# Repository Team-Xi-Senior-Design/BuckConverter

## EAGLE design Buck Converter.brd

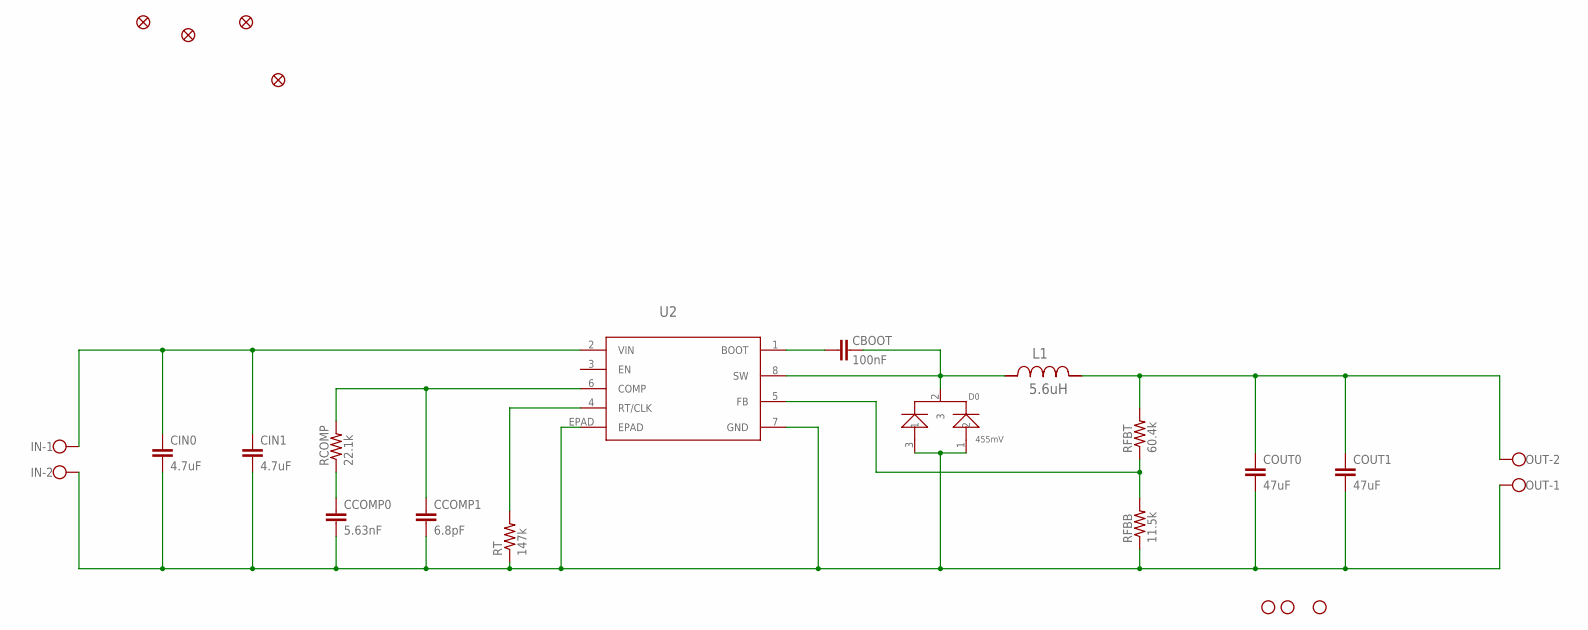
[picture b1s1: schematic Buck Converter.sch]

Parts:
CBOOT: 100nF; C0805
CCOMP0: 5.63nF; C0805
CCOMP1: 6.8pF; C0805
CIN0, CIN1: 4.7uF; C0805
COUT0, COUT1: 47uF; C1206
D0: 455mV; D2PAK-L
FD1, FD2, FD3, FD4: FIDUCIALUFIDUCIAL; FIDUCIAL-MICRO
H1, H2, H3: STAND-OFFTIGHT; STAND-OFF-TIGHT
IN: W237-102
L1: 5.6uH; SDR1307
OUT: W237-102
RCOMP: 22.1k; R0603
RFBB: 11.5k; R0603
RFBT: 60.4k; R0603
RT: 147k; R0603
U2: TPS54540DDARDDA8_3P1X2P4-L; DDA8_3P1X2P4-L

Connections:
COMP: CCOMP1.1, RCOMP.2, U2.6 (COMP)
FB: RFBB.2, RFBT.1, U2.5 (FB)
GND: CCOMP0.2, CCOMP1.2, CIN0.2, CIN1.2, COUT0.2, COUT1.2, D0.1 (2), D0.3 (1), IN.2, OUT.1, RFBB.1, RT.1, U2.7 (GND), U2.EPAD
unnamed: CBOOT.2, U2.1 (BOOT)
unnamed: CCOMP0.1, RCOMP.1
RT_CLK: RT.2, U2.4 (RT/CLK)
SW: CBOOT.1, D0.2 (3), L1.1, U2.8 (SW)
VIN: CIN0.1, CIN1.1, IN.1, U2.2 (VIN)
VOUT: COUT0.1, COUT1.1, L1.2, OUT.2, RFBT.2

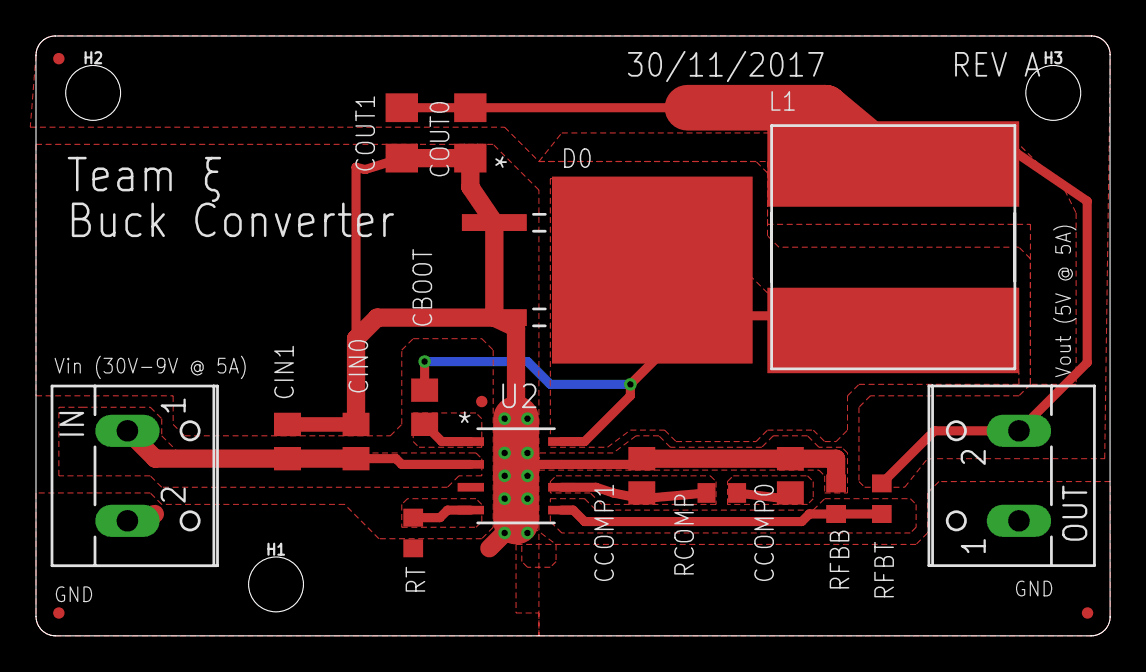
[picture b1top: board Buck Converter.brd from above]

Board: 2 copper layers, 59.7 x 33.3 mm, 23 parts (0 on the bottom side), 9 nets.

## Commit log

2017-12-06 RevA
    Buck Converter RevA complete

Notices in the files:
parts and their libraries:
SparkFun-Hardware: Licensing: Creative Commons ShareAlike 4.0 International - https://creativecommons.org/licenses/by-sa/4.0
